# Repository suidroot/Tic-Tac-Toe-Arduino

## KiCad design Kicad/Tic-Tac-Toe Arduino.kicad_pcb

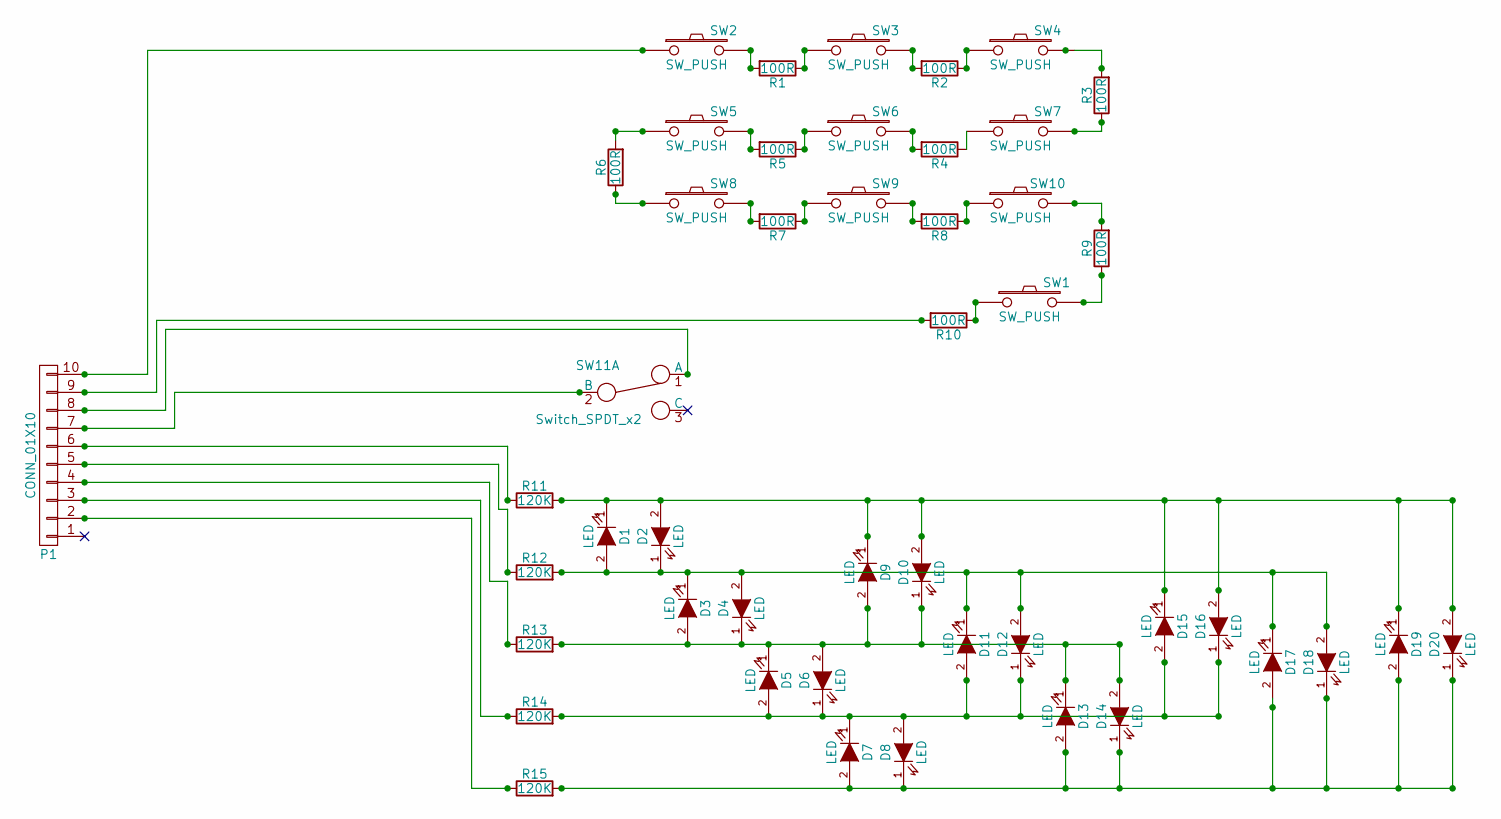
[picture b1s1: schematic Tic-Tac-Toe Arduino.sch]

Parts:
D1, D2, D3, D4, D5, D6, D7, D8, D9, D10, D11, D12, D13, D14, D15, D16, D17, D18, D19, D20: LED; LED-5MM
P1: CONN_01X10; Pin_Header_Straight_1x10
R1, R2, R3, R4, R5, R6, R7, R8, R9, R10: 100R; Resistor_Horizontal_RM30mm
R11, R12, R13, R14, R15: 120K; Resistor_Horizontal_RM30mm
SW1, SW2, SW3, SW4, SW5, SW6, SW7, SW8, SW9, SW10: SW_PUSH; SW_PUSH-12mm
SW11: Switch_SPDT_x2; SW_SPDT_PCM12

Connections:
unnamed: D1.1 (K), D2.2 (A), D9.1 (K), D10.2 (A), D15.1 (K), D16.2 (A), D19.1 (K), D20.2 (A), R11.2
unnamed: D1.2 (A), D2.1 (K), D3.1 (K), D4.2 (A), D11.1 (K), D12.2 (A), D17.1 (K), D18.2 (A), R12.2
unnamed: D3.2 (A), D4.1 (K), D5.1 (K), D6.2 (A), D9.2 (A), D10.1 (K), D13.1 (K), D14.2 (A), R13.2
unnamed: D5.2 (A), D6.1 (K), D7.1 (K), D8.2 (A), D11.2 (A), D12.1 (K), D15.2 (A), D16.1 (K), R14.2
unnamed: D7.2 (A), D8.1 (K), D13.2 (A), D14.1 (K), D17.2 (A), D18.1 (K), D19.2 (A), D20.1 (K), R15.2
unnamed: P1.2, R15.1
unnamed: P1.3, R14.1
unnamed: P1.4, R13.1
unnamed: P1.5, R12.1
unnamed: P1.6, R11.1
unnamed: P1.7, SW11.2 (B)
unnamed: P1.8, SW11.1 (A)
unnamed: P1.9, R10.2
unnamed: P1.10, SW2.1
unnamed: R1.1, SW3.1
unnamed: R1.2, SW2.2
unnamed: R2.1, SW4.1
unnamed: R2.2, SW3.2
unnamed: R3.1, SW7.2
unnamed: R3.2, SW4.2
unnamed: R4.1, SW7.1
unnamed: R4.2, SW6.2
unnamed: R5.1, SW6.1
unnamed: R5.2, SW5.2
unnamed: R6.1, SW8.1
unnamed: R6.2, SW5.1
unnamed: R7.1, SW9.1
unnamed: R7.2, SW8.2
unnamed: R8.1, SW10.1
unnamed: R8.2, SW9.2
unnamed: R9.1, SW1.2
unnamed: R9.2, SW10.2
unnamed: R10.1, SW1.1

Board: 2 copper layers, 47 parts (0 on the bottom side), 33 nets, no tracks yet.
